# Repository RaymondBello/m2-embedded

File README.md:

# m2-embedded - AeroCore v0.1
This project is for M.2 Carrier boards + SOMs

## M.2 Carrier Board 
### Features
- 8 x PWM headers (JST/2.54mm header) (5V/5A Max. Current)
- 2 x I2C Buses
- 2 x SPI Buses
- 2 x IMUs (I2C0 & SPI0)
- 2 x Barometric sensors (I2C1 & SPI1)
- 1 x SD Card (SPI1)
- 3 x UART Serial (GPS & x2 Debug)
- 1 x JTAG port
- 1 x SWD port
- 14.8V Voltage regulator to 5V/5A Max.
- 5V Voltage regulator to 3V3/2A Max.
- 3 x Status LEDs
- Battery current sensing
- USB-C Connector for debug/power
- Video Overlay (Pending)

## M.2 RP2040 SOM
### Features
- 8 x PWM
- 1 x I2C (IMU)
- 2 x SPI (BARO, SDCARD)
- 1 x SWD
- 1 x USB

## M.2 ESP32-S3 SOM
### Features
- 8 x PWM
- 1 x I2C (IMU)
- 2 x SPI
- 1 x USB
- 1 x JTAG

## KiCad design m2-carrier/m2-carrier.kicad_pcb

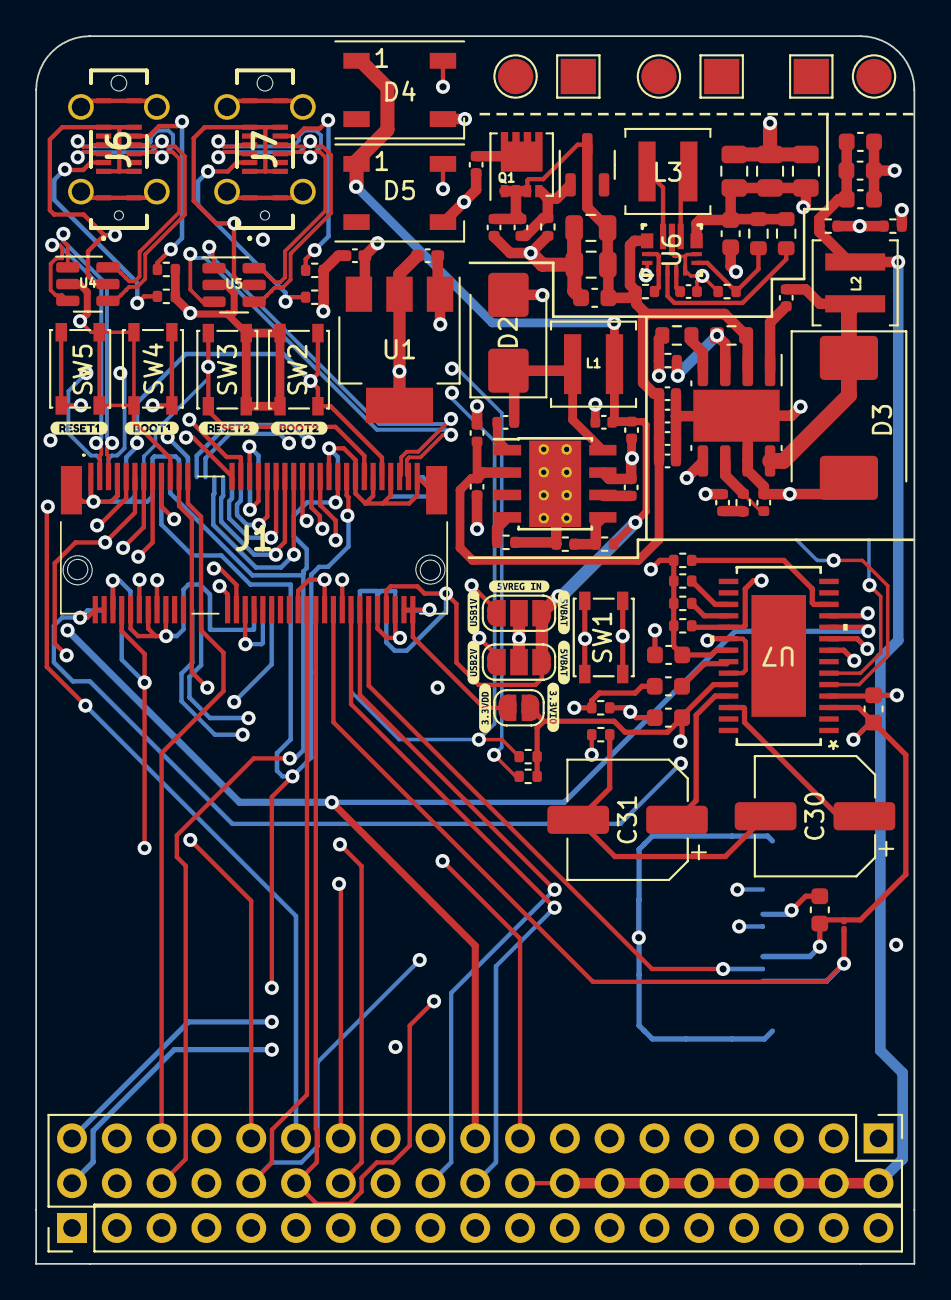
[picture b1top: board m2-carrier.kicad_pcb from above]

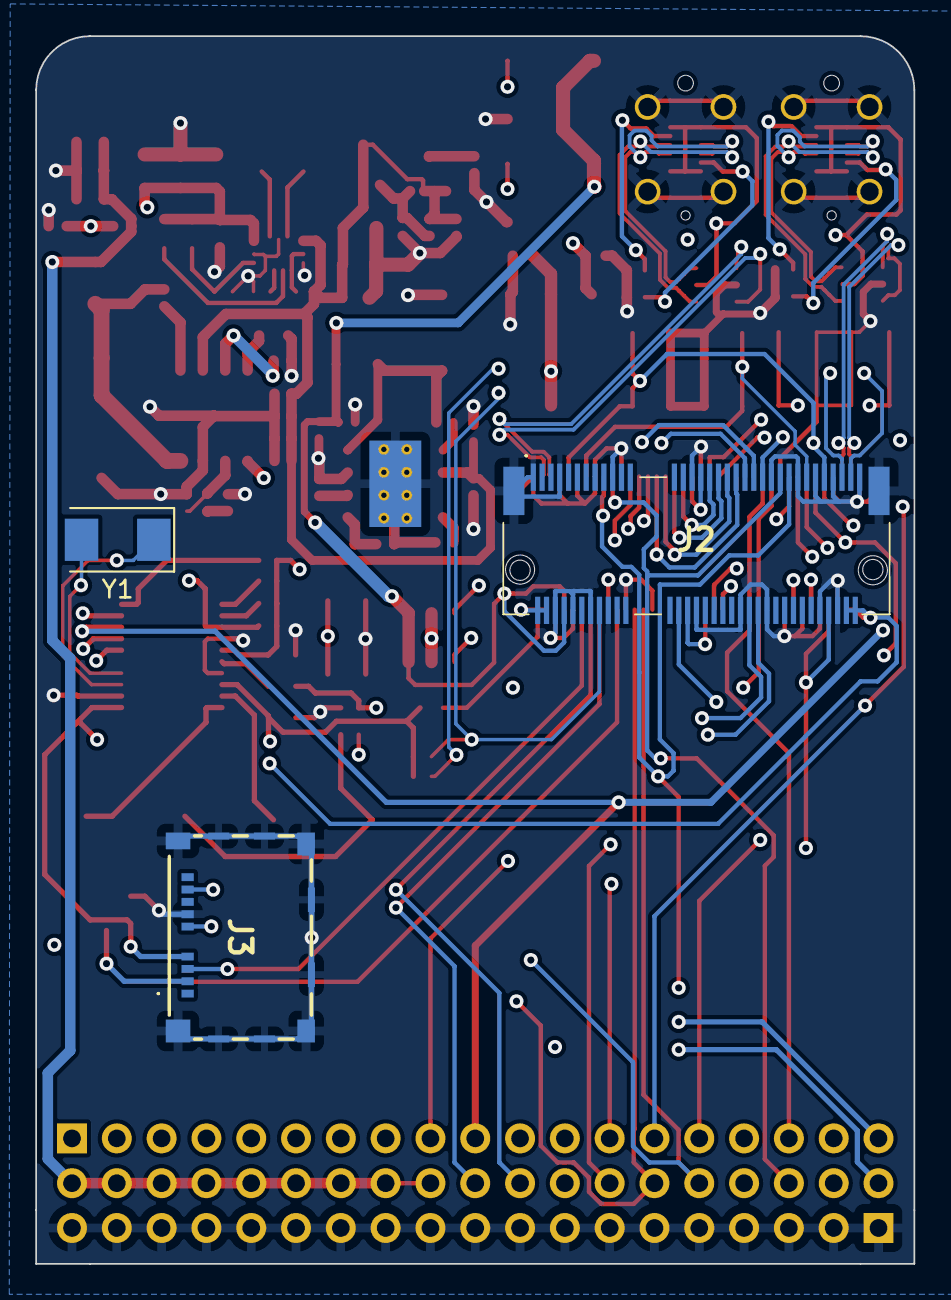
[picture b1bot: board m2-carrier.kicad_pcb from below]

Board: 4 copper layers, 49.8 x 69.6 mm, 112 parts (3 on the bottom side), 93 nets.

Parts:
3V3_IO1: IO_EN; SolderJumper-2_P1.3mm_Open_RoundedPad1.0x1.5mm
5VREG1: USB0; SolderJumper-3_P1.3mm_Open_RoundedPad1.0x1.5mm_NumberLabels
C1, C2, C8, C25: 100nF; C_0402_1005Metric
C3: 10uF; C_0402_1005Metric
C4, C5, C12, C13, C14, C15: 2.2uF; C_0402_1005Metric
C6, C9: 10uF; C_0402_1005Metric_Pad0.74x0.62mm_HandSolder
C7: C_SS; C_0402_1005Metric
C10, C11: 47uF; C_0402_1005Metric
C16: 4700pF; C_0402_1005Metric
C17: 47pF; C_0402_1005Metric
C18: 0.1uF; C_0402_1005Metric
C19, C20, C21: 47uF; C_0603_1608Metric
C22, C26: 10uF; C_0603_1608Metric
C23, C24: 10uF; C_0805_2012Metric
C27, C28, C29: 22uF; C_0805_2012Metric
C30: 220uF; CP_Elec_6.3x5.4
C31: 47uF; CP_Elec_6.3x5.4
C32, C33, C34, C35, C37: 0.1uF; C_0603_1608Metric
D1: MMBZ5242B; SOT-23-3
D2: B340AG; D_SMB
D3: B560C; D_SMC
D4, D5: WS2812B; LED_WS2812B_PLCC4_5.0x5.0mm_P3.2mm
J1, J2: 2199119-4; 21991194
J3: MEM2085-00-115-00-A; MEM20850011500A
J4: HEADER1; PinHeader_2x19_P2.54mm_Vertical
J5: HEADER2; PinHeader_1x19_P2.54mm_Vertical
J6, J7: USB4120-03-C; USB412003C
JP3: USB1; SolderJumper-3_P1.3mm_Open_RoundedPad1.0x1.5mm_NumberLabels
L1: 8.2uH; L_Coilcraft_XAL4020-XXX
L2: 7.2uH; L_Coilcraft_XAL4020-XXX
L3: 1.5uH; L_Coilcraft_XAL4020-XXX
P1: LIPO_VCC; TestPoint_Pad_2.0x2.0mm
P2: LIPO_GND; TestPoint_Pad_D2.0mm
P3: ESC1_VCC; TestPoint_Pad_2.0x2.0mm
P4: ESC1_GND; TestPoint_Pad_D2.0mm
P5: ESC2_VCC; TestPoint_Pad_2.0x2.0mm
P6: ESC2_GND; TestPoint_Pad_D2.0mm
Q1: DMP3013SFV; Diodes_PowerDI3333-8
R1: 12K; R_0402_1005Metric
R2: 49.9K; R_0402_1005Metric
R3: 100K; R_0402_1005Metric
R4: 17.8K; R_0402_1005Metric
R5, R12, R24, R25: 5K1; R_0402_1005Metric
R6: 442K; R_0603_1608Metric
R7: 90.9K; R_0402_1005Metric
R8: 243K; R_0603_1608Metric
R9: 16.9K; R_0402_1005Metric
R10: 53.6K; R_0402_1005Metric
R11: 10.2K; R_0402_1005Metric
R13, R19, R26, R27: 10K; R_0402_1005Metric
R14: 402K; R_0603_1608Metric
R15: 39K; R_0402_1005Metric
R16: 100K; R_0603_1608Metric
R17, R18: 75R; R_0402_1005Metric
R20, R21, R22: 1K; R_0402_1005Metric
R23: 1K; R_01005_0402Metric
SW1: OSD_RESET; SW_SPST_PTS810
SW2: SW_BOOT2; SW_SPST_PTS810
SW3: SW_RESET2; SW_SPST_PTS810
SW4: SW_BOOT1; SW_SPST_PTS810
SW5: SW_RESET1; SW_SPST_PTS810
U1: LD1117S33TR_SOT223; SOT-223-3_TabPin2
U2: LMR16030SDDAR; Texas_HSOP-8-1EP_3.9x4.9mm_P1.27mm_ThermalVias
U3: TPS54560DDAR; Texas_R-PDSO-G8_EP2.95x4.9mm_Mask2.4x3.1mm
U4, U5: USBLC6-2SC6; SOT-23-6
U6: TPS63070RNMR; RNM0015A
U7: AT7456E; 21-0108G_U28E-5_MXM-L
Y1: 27MHz; Crystal_SMD_Abracon_ABM3-2Pin_5.0x3.2mm
kibuzzard-656EB3A8: G***; kibuzzard-656EB3A8
kibuzzard-656EB35F: G***; kibuzzard-656EB35F
kibuzzard-656EB36F: G***; kibuzzard-656EB36F
kibuzzard-656EB39C: G***; kibuzzard-656EB39C
kibuzzard-657F4B2F: G***; kibuzzard-657F4B2F
kibuzzard-657F4B16: G***; kibuzzard-657F4B16
kibuzzard-657F4B96, kibuzzard-657F4B96#2: G***; kibuzzard-657F4B96
kibuzzard-657F4C86: G***; kibuzzard-657F4C86
kibuzzard-657F4D6E: G***; kibuzzard-657F4D6E
kibuzzard-657F4D51: G***; kibuzzard-657F4D51

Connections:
5V_VREG_IN: 5VREG1.2 (C), C6.1, JP3.2 (C), U1.3 (VI)
/HEADERS/CON_CAM_VIN: C33.2, J4.37, R18.1
/HEADERS/CON_VTX_VOUT: J4.38, R17.2
/M.2 SOCKET/M2_JTAG_TCK: J1.44, J2.44
/M.2 SOCKET/M2_JTAG_TDI: J1.40, J2.40
/M.2 SOCKET/M2_JTAG_TDO: J1.42, J2.42
/M.2 SOCKET/M2_JTAG_TMS: J1.46, J2.46
/M.2 SOCKET/M2_SWD_SCK: J1.20, J2.20
/M.2 SOCKET/M2_SWD_SDIO: J1.22, J2.22
/POWER/5V_FB: R10.2, R11.1, U3.5 (FB)
/POWER/15VCC: C2.1, C3.1, C4.1, C5.1, C12.1, C13.1, C14.1, C15.1, C22.1, C23.1, C24.1, D1.3 (K), Q1.1 (S), Q1.2 (S), Q1.3 (S), R6.1, R13.1, U2.2 (VIN), U3.2 (VIN), U6.12 (VIN), U6.13 (VIN)
/POWER/COMP: C17.1, R9.1, U3.6 (COMP)
/POWER/VAUX: C25.1, U6.3 (VAUX)
/VIDEO/LOS: R22.2, U7.12 (LOS)
/VIDEO/VIN: C33.1, U7.22 (VIN)
/VIDEO/~HSYNC: R20.2, U7.18 (*HSYNC)
/VIDEO/~RESET: R19.1, SW1.2, U7.19 (*RESET)
/VIDEO/~VSYNC: R21.2, U7.17 (*VSYNC)
ESD_USB0_DN: J6.A7 (DN1), J6.B7 (DN2), U4.6 (I/O1)
ESD_USB0_DP: J6.A6 (DP1), J6.B6 (DP2), U4.4 (I/O2)
ESD_USB1_DN: J7.A7 (DN1), J7.B7 (DN2), U5.6 (I/O1)
ESD_USB1_DP: J7.A6 (DP1), J7.B6 (DP2), U5.4 (I/O2)
FB: R3.2, R4.1, U2.5 (FB)
GND: C1.2, C3.2, C4.2, C5.2, C6.2, C7.2, C9.2, C10.1, C11.1, C12.2, C13.2, C14.2, C15.2, C16.2, C17.2, C19.2, C20.2, C21.2, C22.2, C23.2, C24.2, C25.2, C26.2, C27.2, C28.2, C29.2, C32.1, C34.2, C35.2, C37.2, D2.2 (A), D3.2 (A), D4.3 (VSS), D5.3 (VSS), J1.1, J1.6, J1.7, J1.10, J1.14, J1.18, J1.19, J1.37, J1.38, J1.48, J1.54, J1.55, J1.61, J1.65, J1.66, J1.69, J1.70, J1.75, J1.MP1, J1.MP2, J2.1, J2.6, J2.7, J2.10, J2.14, J2.18, J2.19, J2.37, J2.38, J2.48, J2.54, J2.55, J2.61, J2.65, J2.66, J2.69, J2.70, J2.75, J2.MP1, J2.MP2, J3.G1 (GND_1), J3.G2 (GND_2), J3.G3 (GND_3), J3.G4 (GND_4), J3.G5 (GND_5), J3.G6 (GND_6), J3.G7 (GND_7), J3.G8 (GND_8), J3.G9 (GND_9), J3.G10 (GND_10), J3.P6 (VSS), J5.1, J5.2, J5.3, J5.4, J5.5, J5.6, J5.7, J5.8, J5.9, J5.10, J5.11, J5.12, J5.13, J5.14, J5.15, J5.16, J5.17, J5.18, J5.19, J6.A1 (GND_1), J6.A12 (GND_2), J6.B1 (GND_3), J6.B12 (GND_4), J6.MH1, J6.MH2, J6.MH3, J6.MH4, J7.A1 (GND_1), J7.A12 (GND_2), J7.B1 (GND_3), J7.B12 (GND_4), J7.MH1, J7.MH2, J7.MH3, J7.MH4, P2.1 (PAD), P4.1 (PAD), P6.1 (PAD), R1.2, R2.2, R4.2, R5.2, R7.2, R8.2, R11.2, R12.2, R15.2, R18.2, R24.2, R25.2, SW1.1, SW2.1, SW3.2, SW4.1, SW5.2, U1.1 (GND), U2.7 (BOOT), U2.9 (AGND), U3.7 (GND), U3.9 (GND), U4.2 (GND), U5.2 (GND), U6.4 (GND), U6.6 (FB2), U6.10 (PGND), U6.15 (VSEL), U7.4 (DGND), U7.20 (AGND), U7.23 (PGND)
unnamed: C16.1, R9.2
unnamed: C30.2, C31.2, R17.1
unnamed: C2.2, D1.1 (A), Q1.4 (G), R1.1
unnamed: C8.2, D2.1 (K), L1.1, U2.8 (SW)
unnamed: C18.1, D3.1 (K), L2.1, U3.8 (SW)
unnamed: J6.A5 (CC1), R25.1
unnamed: J6.B5 (CC2), R24.1
unnamed: J7.A5 (CC1), R5.1
unnamed: J7.B5 (CC2), R12.1
unnamed: R2.1, U2.4 (PG)
unnamed: C8.1, U2.1 (PGND)
unnamed: C7.1, U2.6 (VCC)
unnamed: C18.2, U3.1 (BOOT)
unnamed: R6.2, R7.1, U3.3 (EN)
unnamed: R8.1, U3.4 (RT/CLK)
unnamed: R13.2, U6.1 (PS_SYNC), U6.14 (EN)
unnamed: R14.2, R15.1, U6.5 (FB)
unnamed: L3.1, U6.11 (L1)
unnamed: L3.2, U6.9 (L2)
unnamed: R16.2, U6.2 (PG)
unnamed: U7.5 (CLKIN), Y1.1
unnamed: C31.1, U7.25 (SAG)
unnamed: C30.1, U7.26 (VOUT)
unnamed: U7.6 (XFB), Y1.2
SOM1_BOOT: J1.12, J2.12, SW4.2
SOM1_I2C0_SCK: J1.23, J2.23, J4.33
SOM1_I2C0_SDA: J1.21, J2.21, J4.31
SOM1_LED1_DIN: D4.4 (DIN), J1.32, J2.32
SOM1_RESET: J1.16, J2.16, R26.1, SW5.1
SOM1_SPI0_CS0: J1.15, J2.15, U7.8 (*CS)
SOM1_SPI0_CS1: J1.17, J2.17, J4.25
SOM1_SPI0_MISO: J1.11, J2.11, J4.21, U7.11 (SDOUT)
SOM1_SPI0_MOSI: J1.13, J2.13, J4.23, U7.9 (SDIN)
SOM1_SPI0_SCK: J1.9, J2.9, J4.19, U7.10 (SCLK)
SOM1_SPI1_CS0: J1.56, J2.56, J3.P2 (CD/DAT3), R23.2
SOM1_SPI1_CS1: J1.58, J2.58, J4.26
SOM1_SPI1_MISO: J1.62, J2.62, J3.P7 (DAT0), J4.22
SOM1_SPI1_MOSI: J1.64, J2.64, J3.P3 (CMD), J4.24
SOM1_SPI1_SCK: J1.60, J2.60, J3.P5 (CLK), J4.20
SOM1_UART0_RX: J1.33, J2.33, J4.27
SOM1_UART0_TX: J1.35, J2.35, J4.29
SOM1_USB+: J1.3, J2.3, U4.3 (I/O2)
SOM1_USB-: J1.5, J2.5, U4.1 (I/O1)
SOM1_USB_VBUS: 5VREG1.1 (A), J6.A4 (VBUS_1), J6.A9 (VBUS_2), J6.B4 (VBUS_3), J6.B9 (VBUS_4), U4.5 (VBUS)
SOM2_BOOT: J1.67, J2.67, SW2.2
SOM2_I2C1_SCK: J1.57, J2.57, J4.34
SOM2_I2C1_SDA: J1.59, J2.59, J4.32
SOM2_LED2_DIN: D5.4 (DIN), J1.34, J2.34
SOM2_RESET: J1.63, J2.63, R27.1, SW3.1
SOM2_UART1_RX: J1.50, J2.50, J4.30
SOM2_UART1_TX: J1.52, J2.52, J4.28
SOM2_USB+: J1.73, J2.73, U5.3 (I/O2)
SOM2_USB-: J1.71, J2.71, U5.1 (I/O1)
SOM2_USB_VBUS: J7.A4 (VBUS_1), J7.A9 (VBUS_2), J7.B4 (VBUS_3), J7.B9 (VBUS_4), JP3.1 (A), U5.5 (VBUS)
SOM_5V_SERVO: C19.1, C20.1, C21.1, J4.2, J4.4, J4.6, J4.8, J4.10, J4.12, J4.14, J4.16, J4.18, L2.2, R10.1
SOM_9V_CAMERA: C26.1, C27.1, C28.1, C29.1, J4.36, R14.1, R16.1, U6.7 (VOUT), U6.8 (VOUT)
SOM_FC_3V3: 3V3_IO1.2 (B), C9.1, J1.2, J1.4, J1.72, J1.74, J2.2, J2.4, J2.72, J2.74, U1.2 (VO)
SOM_FC_5VDD: 5VREG1.3 (B), C10.2, C11.2, D4.1 (VDD), D5.1 (VDD), J1.8, J1.68, J2.8, J2.68, JP3.3 (B), L1.2, R3.1
SOM_IO_3V3: 3V3_IO1.1 (A), C32.2, C34.1, C35.1, C37.1, J3.P4 (VDD), J4.35, R19.2, R20.1, R21.1, R22.1, R23.1, R26.2, R27.2, U7.3 (DVDD), U7.21 (AVDD), U7.24 (PVDD)
SOM_RC_INPUT: J1.36, J2.36, J4.17
SOM_SERVO1: J1.39, J2.39, J4.15
SOM_SERVO2: J1.41, J2.41, J4.13
SOM_SERVO3: J1.43, J2.43, J4.11
SOM_SERVO4: J1.45, J2.45, J4.9
SOM_SERVO5: J1.47, J2.47, J4.7
SOM_SERVO6: J1.49, J2.49, J4.5
SOM_SERVO7: J1.51, J2.51, J4.3
SOM_SERVO8: J1.53, J2.53, J4.1
VCC: C1.1, P1.1 (PAD), P3.1 (PAD), P5.1 (PAD), Q1.5 (D)

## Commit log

2023-11-28 Updating documentation
2023-11-29 new stuff
2023-11-29 AeroCore v0.1
2023-11-30 added video IC
2023-11-30 Populated OSD IC
2023-12-06 Added base board
2024-02-29 added stuff
